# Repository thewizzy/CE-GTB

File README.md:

CE-GTB
======

Getting to Blinky

A project for starting in KiCad. 
Similar to Hello World and Blinking an LED using a micro.

http://www.youtube.com/user/contextualelectronic

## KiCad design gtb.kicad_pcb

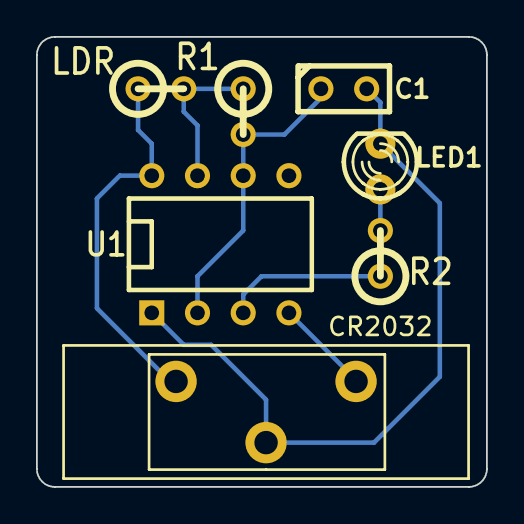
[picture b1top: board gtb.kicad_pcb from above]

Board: 2 copper layers, 25.0 x 25.0 mm, 7 parts (0 on the bottom side), 6 nets.

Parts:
BT1: CR2032; CR2032-Vert-DIP
C1: 1uF; C1
LDR: VR; R1
LED1: LED; LED-3MM
R1: 470K; R1
R2: 1K; R1
U1: 7555; DIP-8__300

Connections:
GND: BT1.2, C1.2, LED1.2, U1.1
unnamed: C1.1, R1.2, U1.2, U1.6
unnamed: R2.1, U1.3
unnamed: LDR.2, R1.1, U1.7
unnamed: LED1.1, R2.2
VCC: BT1.1, LDR.1, U1.4, U1.8

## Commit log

2013-11-12 Uploading Project
    Completed project uploaded

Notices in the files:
gtb.kicad_pcb:
CC BY 3.0
